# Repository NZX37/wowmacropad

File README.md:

# wowmacropad

wowmacropad is a macropad with a joystick on the side, a screen and a rotary encoder as well as two status leds and is rechargeable!

## Features

- ESP32-S3 powered with bluetooth
- USB-C connection
- joystick placed near thumb
- rotary encoder
- Status LEDs
- tft screen

## Design files

KiCad source files are in [`kicad files/`](kicad%20files/). The schematic and board previews are shown below.

| Schematic | PCB layout | CAD |
| --- | --- | --- |
|  |  |  |

## Manufacturing

Ready-to-upload Gerber and drill files are in [`Production Files/`](Production%20Files/).

For a new or modified board revision, open `breadESP32.kicad_pcb` in KiCad and regenerate fabrication outputs from that board before ordering. Check the board outline and manufacturer design rules against your chosen fabricator.

## Bill of materials

# Bill of Materials (BOM)

# Bill of Materials (BOM)

| Item | Qty | Supplier | Cost/Item (USD) | Total Cost (USD) | Link |
|---|---:|---|---:|---:|---|
| ESP32-S3-DevKit-Lipo | 2 | Mouser | $12.76 | $25.52 | [Mouser](https://www.mouser.sg/en/ProductDetail/Olimex-Ltd/ESP32-S3-DevKit-Lipo?qs=Imq1NPwxi76FgMDg4cnCbQ%3D%3D) |
| LCD TFT 1.54" ST7789 | 1 | Mouser | $23.80 | $23.80 | [Mouser](https://www.mouser.sg/en/ProductDetail/Adafruit/3787?qs=wUXugUrL1qx0Txb5soDymA%3D%3D) |
| PCB | 1 | JLCPCB | $10.00 | $10.00 | [JLCPCB](https://jlcpcb.com) |
| Rotating Encoder with Switch 20mm Plum | 2 | Mouser | $2.35 | $4.70 | [Mouser](https://www.mouser.sg/en/ProductDetail/Bourns/PEC16-2220F-N0024?qs=7YHpgRs8DgxGDEH3MBmXIA%3D%3D) |
| Estimated Total Shipping | 1 | — | — | $0.00 | — |

## Cost Summary

| Description | Amount (USD) |
|---|---:|
| Components Subtotal | $64.02 |
| Estimated Shipping | $0.00 |
| **Grand Total** | **$64.02** |

## Cost Summary

| Description | Amount (USD) |
|---|---:|
| Components Subtotal | $54.09 |
| Estimated Shipping | $8.69 |
| **Grand Total** | **$62.78** |

See [`BOM.md`](BOM.md) for the full component list. The TP4056 charger module is external and is not included in this assembly BOM. The project journal is in [`JOURNAL.md`](JOURNAL.md), and the `Firmware/` folder contains a minimal Arduino sketch.

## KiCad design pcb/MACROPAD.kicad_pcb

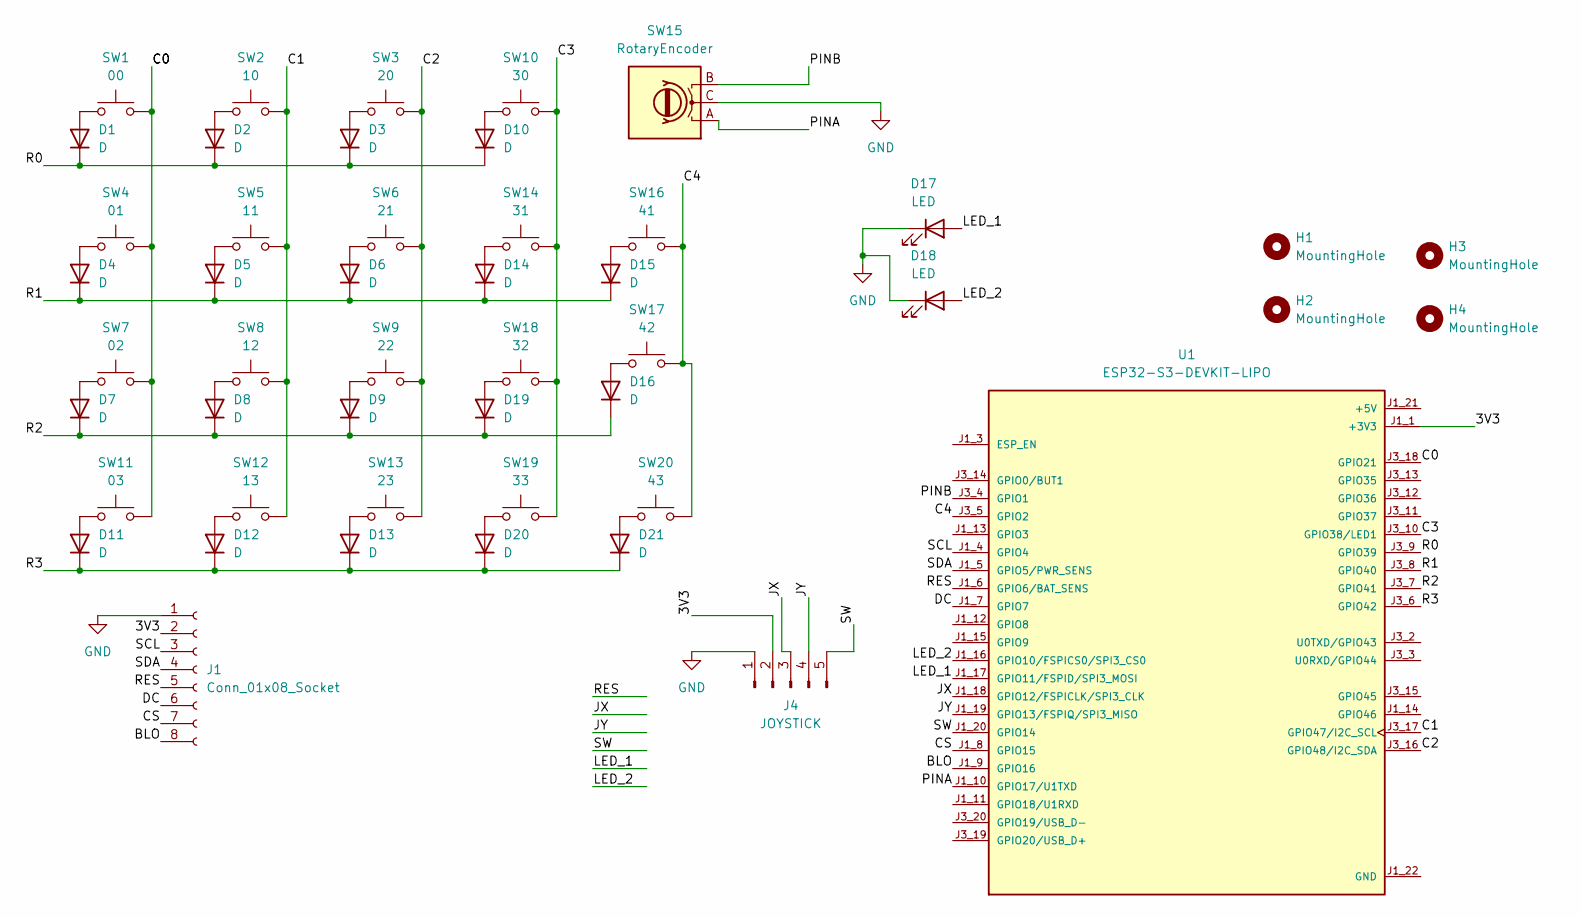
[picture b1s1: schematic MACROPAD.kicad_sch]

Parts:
D1, D2, D3, D4, D5, D6, D7, D8, D9, D10, D11, D12, D13, D14, D15, D16, D19, D20, D21: D; D_DO-35_SOD27_P7.62mm_Horizontal
D17, D18: LED; LED_D5.0mm
H1, H2, H3, H4: MountingHole; MountingHole_3.5mm
J1: Conn_01x08_Socket; PinSocket_1x08_P2.54mm_Vertical
J4: JOYSTICK; PinSocket_1x05_P2.54mm_Vertical
SW1: 00; SW_Hotswap_Kailh_MX_1.00u
SW2: 10; SW_Hotswap_Kailh_MX_1.00u
SW3: 20; SW_Hotswap_Kailh_MX_1.00u
SW4: 01; SW_Hotswap_Kailh_MX_1.00u
SW5: 11; SW_Hotswap_Kailh_MX_1.00u
SW6: 21; SW_Hotswap_Kailh_MX_1.00u
SW7: 02; SW_Hotswap_Kailh_MX_1.00u
SW8: 12; SW_Hotswap_Kailh_MX_1.00u
SW9: 22; SW_Hotswap_Kailh_MX_1.00u
SW10: 30; SW_Hotswap_Kailh_MX_1.00u
SW11: 03; SW_Hotswap_Kailh_MX_1.00u
SW12: 13; SW_Hotswap_Kailh_MX_1.00u
SW13: 23; SW_Hotswap_Kailh_MX_1.00u
SW14: 31; SW_Hotswap_Kailh_MX_1.00u
SW15: RotaryEncoder; RotaryEncoder_Alps_EC11E-Switch_Vertical_H20mm
SW16: 41; SW_Hotswap_Kailh_MX_1.00u
SW17: 42; SW_Hotswap_Kailh_MX_1.00u
SW18: 32; SW_Hotswap_Kailh_MX_1.00u
SW19: 33; SW_Hotswap_Kailh_MX_1.00u
SW20: 43; SW_Hotswap_Kailh_MX_1.00u
U1: ESP32-S3-DEVKIT-LIPO; XCVR_ESP32-S3-DEVKIT-LIPO; PARTREV B

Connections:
+3V3: J1.2, J4.2, U1.J1_1 (+3V3), U1.J1_2 (+3V3)
/BLO: J1.8, U1.J1_9 (GPIO16)
/C0: SW1.2, SW4.2, SW7.2, SW11.2, U1.J3_18 (GPIO21)
/C1: SW2.2, SW5.2, SW8.2, SW12.2, U1.J3_17 (GPIO47/I2C_SCL)
/C2: SW3.2, SW6.2, SW9.2, SW13.2, U1.J3_16 (GPIO48/I2C_SDA)
/C3: SW10.2, SW14.2, SW18.2, SW19.2, U1.J3_10 (GPIO38/LED1)
/C4: SW16.2, SW17.2, SW20.2, U1.J3_5 (GPIO2)
/CS: J1.7, U1.J1_8 (GPIO15)
/DC: J1.6, U1.J1_7 (GPIO7)
/JX: J4.3, U1.J1_18 (GPIO12/FSPICLK/SPI3_CLK)
/JY: J4.4, U1.J1_19 (GPIO13/FSPIQ/SPI3_MISO)
/LED_1: D17.2 (A), U1.J1_17 (GPIO11/FSPID/SPI3_MOSI)
/LED_2: D18.2 (A), U1.J1_16 (GPIO10/FSPICS0/SPI3_CS0)
/PINA: SW15.A, U1.J1_10 (GPIO17/U1TXD)
/PINB: SW15.B, U1.J3_4 (GPIO1)
/R0: D1.1 (K), D2.1 (K), D3.1 (K), D10.1 (K), U1.J3_9 (GPIO39)
/R1: D4.1 (K), D5.1 (K), D6.1 (K), D14.1 (K), D15.1 (K), U1.J3_8 (GPIO40)
/R2: D7.1 (K), D8.1 (K), D9.1 (K), D16.1 (K), D19.1 (K), U1.J3_7 (GPIO41)
/R3: D11.1 (K), D12.1 (K), D13.1 (K), D20.1 (K), D21.1 (K), U1.J3_6 (GPIO42)
/RES: J1.5, U1.J1_6 (GPIO6/BAT_SENS)
/SCL: J1.3, U1.J1_4 (GPIO4)
/SDA: J1.4, U1.J1_5 (GPIO5/PWR_SENS)
/SW: J4.5, U1.J1_20 (GPIO14)
unnamed: D1.2 (A), SW1.1
unnamed: D2.2 (A), SW2.1
unnamed: D3.2 (A), SW3.1
unnamed: D4.2 (A), SW4.1
unnamed: D5.2 (A), SW5.1
unnamed: D6.2 (A), SW6.1
unnamed: D7.2 (A), SW7.1
unnamed: D8.2 (A), SW8.1
unnamed: D9.2 (A), SW9.1
unnamed: D10.2 (A), SW10.1
unnamed: D11.2 (A), SW11.1
unnamed: D12.2 (A), SW12.1
unnamed: D13.2 (A), SW13.1
unnamed: D14.2 (A), SW14.1
unnamed: D15.2 (A), SW16.1
unnamed: D16.2 (A), SW17.1
unnamed: D19.2 (A), SW18.1
unnamed: D20.2 (A), SW19.1
unnamed: D21.2 (A), SW20.1

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
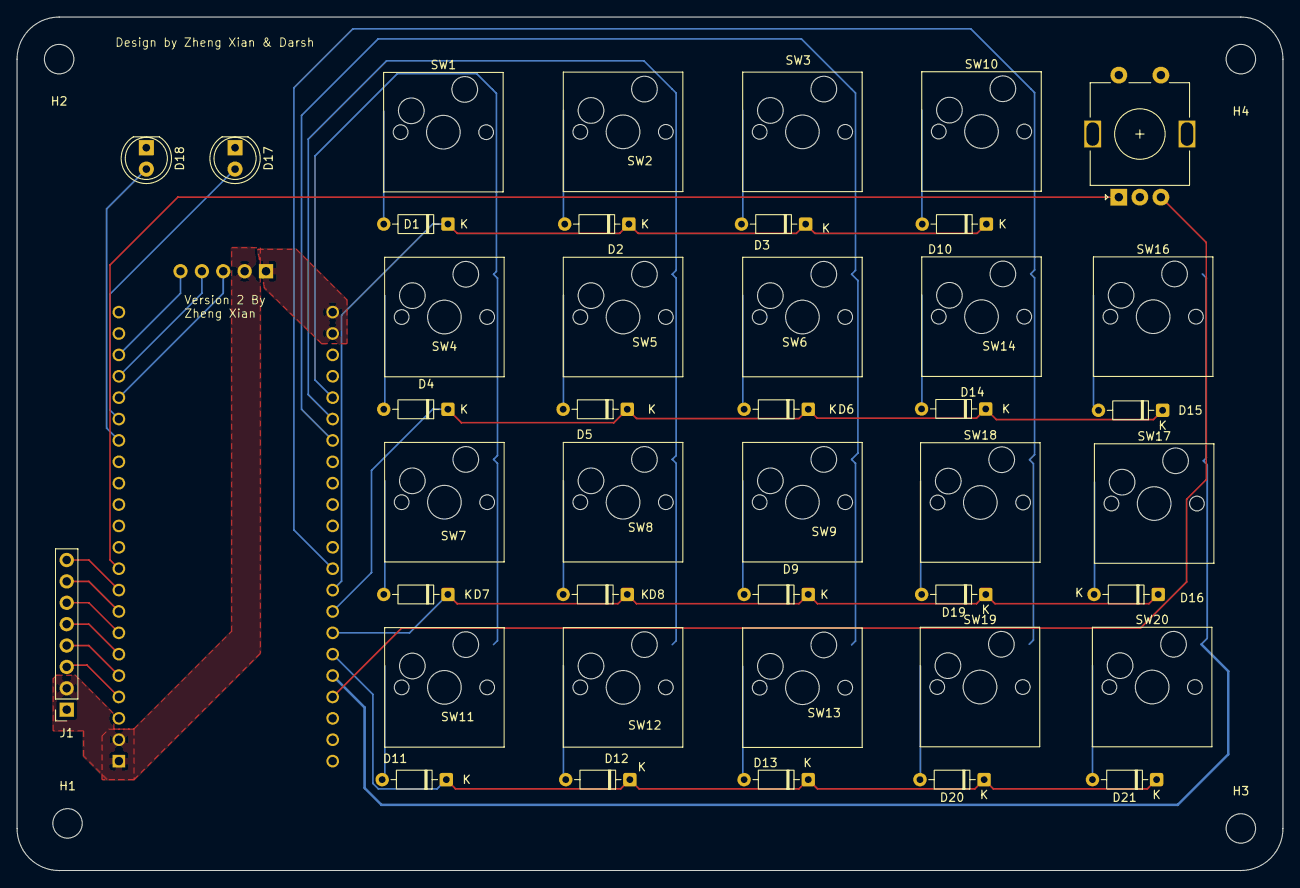
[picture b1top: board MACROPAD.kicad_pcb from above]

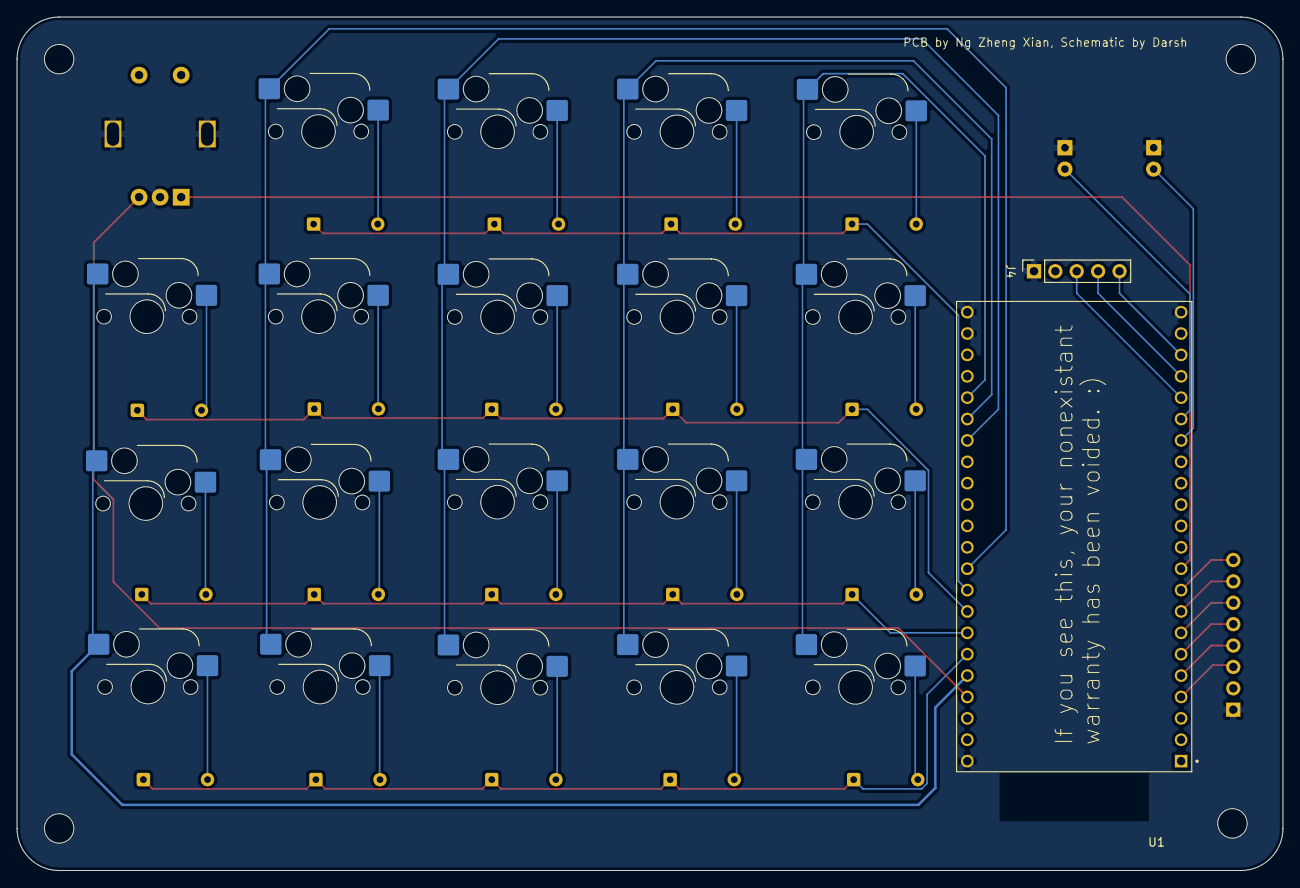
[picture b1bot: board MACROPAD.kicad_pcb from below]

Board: 2 copper layers, 150.4 x 101.4 mm, 48 parts (2 on the bottom side), 43 nets.
